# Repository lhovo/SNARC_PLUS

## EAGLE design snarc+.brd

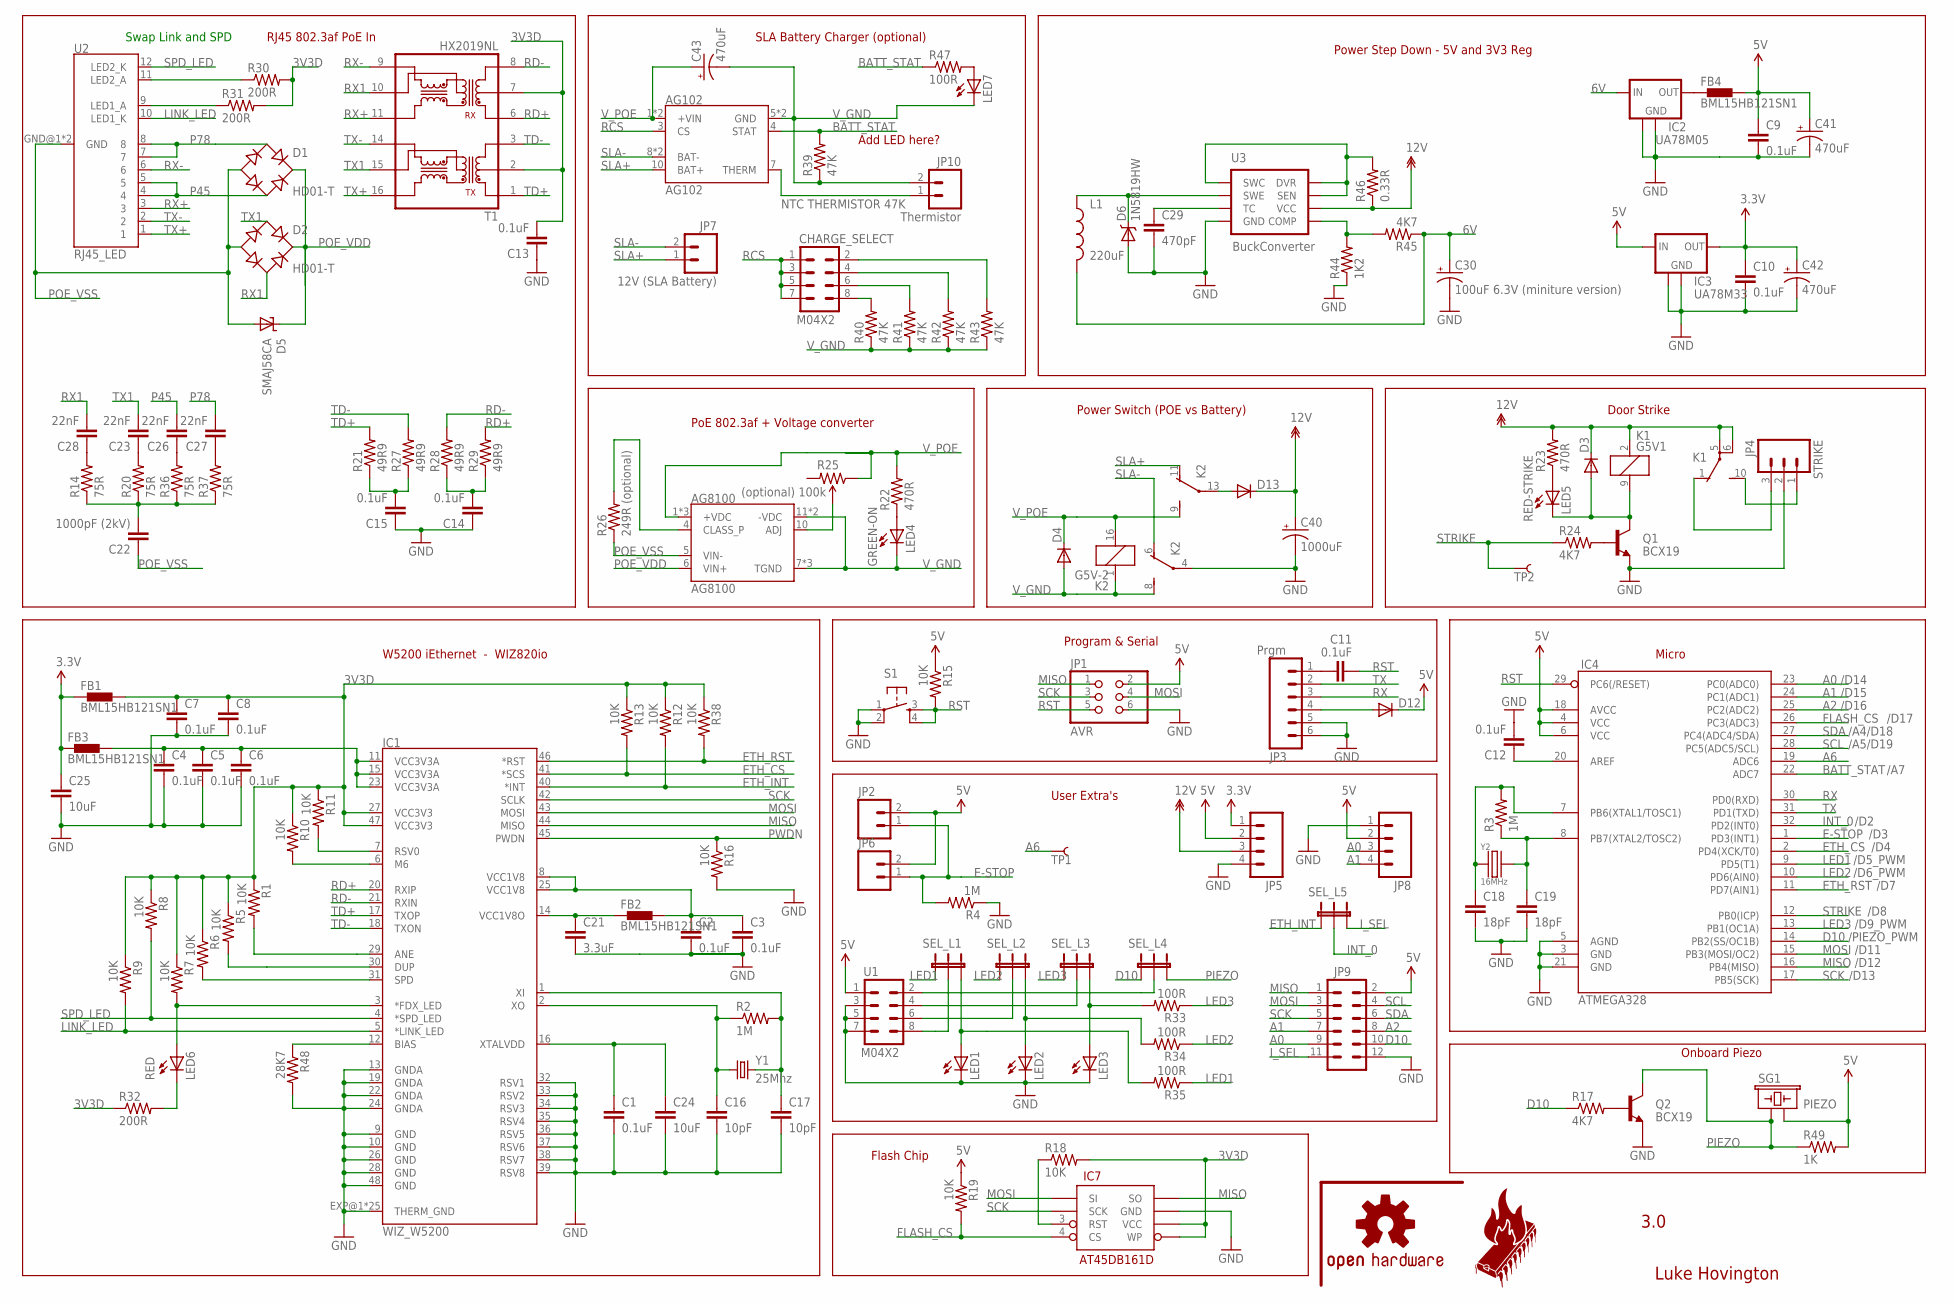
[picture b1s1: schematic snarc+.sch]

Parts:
AG102: AG102
AG8100: AG8100
C1, C2, C3, C4, C5, C6, C7, C8, C9, C10, C11, C12, C13, C14, C15: 0.1uF; 0402-CAP
C16, C17: 10pF; 0402-CAP
C18, C19: 18pF; 0402-CAP
C21: 3.3uF; 0402-CAP
C22: 1000pF (2kV); 0402-CAP
C23, C26, C27, C28: 22nF; 0402-CAP
C24, C25: 10uF; 0603-CAP
C29: 470pF; 0402-CAP
C30: 100uF 6.3V (miniture version); PANASONIC_C
C40: 1000uF; PANASONIC_H13
C41, C42, C43: 470uF; PANASONIC_E
CHARGE_SELECT: M04X2; 2X4
D1, D2: HD01-T; MBS
D3, D4, D12, D13: DIODESOD; SOD-323
D5: SMAJ58CA; SMBJ
D6: 1N5819HW; SOD-123
FB1, FB2, FB3, FB4: BML15HB121SN1; 0402
IC1: WIZ_W5200; QFN48
IC2: UA78M05; SOT223
IC3: UA78M33; SOT223
IC4: ATMEGA328; TQFP32-08
IC7: AT45DB161D; SO08-EIAJ
JP1: AVR; 2X03
JP2: M023.5MM; SCREWTERMINAL-3.5MM-2
JP3: Prgm; 1X06_SMD_STRAIGHT
JP4: STRIKE; SCREWTERMINAL-3.5MM-3
JP5: M04SMD; 1X04-SMD
JP6: M021X02_NO_SILK; 1X02_NO_SILK
JP7: 12V (SLA Battery); SCREWTERMINAL-3.5MM-2
JP8: M04POLAR; MOLEX-1X4
JP9: M05x2_SMD; 2X6-SHROUDED_SMD
JP10: Thermistor; SCREWTERMINAL-3.5MM-2
K1: G5V1; MPN G5V-1-DC24
K2: G5V-2
L1: 220uF; SRN
LED1, LED2, LED3, LED7: LED0603; LED-0603
LED4: GREEN-ON; LED-0603
LED5: RED-STRIKE; LED-0603
LED6: RED; LED-0603
Q1, Q2: BCX19; SOT23-3
R1, R5, R6, R7, R8, R9, R10, R11, R12, R13, R15, R16, R18, R19, R38: 10K; 0402-RES
R2, R3: 1M; 0402-RES
R4: 1M; 0603-RES
R14, R20, R36, R37: 75R; 0402-RES
R17, R24, R45: 4K7; 0402-RES
R21, R27, R28, R29: 49R9; 0402-RES
R22, R23: 470R; 0402-RES
R25: (optional) 100k; TRIMPOT-3MM
R26: 249R (optional); 1206
R30, R31, R32: 200R; 0402-RES
R33, R34, R35, R47: 100R; 0402-RES
R39, R40, R41, R42, R43: 47K; 0402-RES
R44: 1K2; 0402-RES
R46: 0.33R; 0402-RES
R48: 28K7; 0402-RES
R49: 1K; 0402-RES
S1: TAC_SWITCHSMD; TACTILE_SWITCH_SMD
SEL_L1, SEL_L2, SEL_L3, SEL_L4, SEL_L5: JUMPER-32-3; SJ_3_PASTE2&3
SG1: PIEZO; PB158-BUZZER
T1: HX2019NL; HXXXX
TP1, TP2: TEST-POINT3X5; PAD.03X.05
U1: M04X2; 2X4
U2: RJ45_LED; RJHSE-5484
U3: BuckConverter; SO08
U$15: OSHW-LOGOL; OSHW-LOGO-L
U$16: HSBNE_LOGOMED; HSBNE_MED
Y1: 25Mhz; CRYSTAL-SMD-2.5X2-ABM10
Y2: 16MHz; XTAL-CSX750

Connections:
3.3V: C10.1, C25.1, C42.+, FB1.1, FB3.1, IC3.3 (OUT), JP5.1
3V3A: C4.1, C5.1, C6.1, FB3.2, IC1.11 (VCC3V3A), IC1.15 (VCC3V3A), IC1.23 (VCC3V3A)
3V3D: C7.1, C8.1, C13.2, FB1.2, IC1.27 (VCC3V3), IC1.47 (VCC3V3), IC7.5 (WP), IC7.6 (VCC), R1.1, R5.1, R6.1, R7.1, R8.1, R9.1, R10.1, R11.1, R12.1, R13.1, R18.2, R30.2, R31.2, R32.1, R38.1, T1.2, T1.7
5V: C9.1, C41.+, D12.1 (C), FB4.2, IC3.1 (IN), IC4.4 (VCC), IC4.6 (VCC), IC4.18 (AVCC), JP1.2, JP2.2, JP5.2, JP6.2, JP8.2, JP9.2, R15.1, R19.1, R49.2, SG1.P$2 (2), U1.1
6V: C30.+, IC2.1 (IN), L1.P$2 (2), R45.1
12V: C40.+, D3.1 (C), D13.1 (C), JP5.3, K1.2 (1), K1.5, K1.6, R23.2, R46.1, U3.6 (VCC)
A0: IC4.23 (PC0(ADC0)), JP8.3, JP9.9
A1: IC4.24 (PC1(ADC1)), JP8.4, JP9.7
A2: IC4.25 (PC2(ADC2)), JP9.8
A6: IC4.19 (ADC6), TP1.P$1
AREF1: C12.1, IC4.20 (AREF)
BATT_STAT: AG102.4 (STAT), IC4.22 (ADC7), R39.2, R47.1
BATT_THERM: AG102.7 (THERM), JP10.1
D10: IC4.14 (PB2(SS/OC1B)), JP9.10, R17.1, SEL_L4.1
E-STOP: IC4.1 (PD3(INT1)), JP2.1, JP6.1, R4.2
ETH_CS: IC1.41 (*SCS), IC4.2 (PD4(XCK/T0)), R13.2
ETH_INT: IC1.40 (*INT), R12.2, SEL_L5.1
ETH_RST: IC1.46 (*RST), IC4.11 (PD7(AIN1)), R38.2
FDX_LED: IC1.3 (*FDX_LED), LED6.A, R7.2
FLASH_CS: IC4.26 (PC3(ADC3)), IC7.4 (CS), R19.2
GND: C1.2, C2.2, C3.2, C4.2, C5.2, C6.2, C7.2, C8.2, C9.2, C10.2, C12.2, C13.1, C14.1, C15.1, C16.2, C17.2, C18.2, C19.2, C21.2, C24.2, C25.2, C29.2, C30.-, C40.-, C41.-, C42.-, D6.2 (A), IC1.9 (GND), IC1.10 (GND), IC1.13 (GNDA), IC1.19 (GNDA), IC1.22 (GNDA), IC1.24 (GNDA), IC1.26 (GND), IC1.28 (GND), IC1.32 (RSV1), IC1.33 (RSV2), IC1.34 (RSV3), IC1.35 (RSV4), IC1.36 (RSV5), IC1.37 (RSV6), IC1.38 (RSV7), IC1.39 (RSV8), IC1.48 (GND), IC1.EXP@1 (THERM_GND), IC1.EXP@2 (THERM_GND), IC1.EXP@3 (THERM_GND), IC1.EXP@4 (THERM_GND), IC1.EXP@5 (THERM_GND), IC1.EXP@6 (THERM_GND), IC1.EXP@7 (THERM_GND), IC1.EXP@8 (THERM_GND), IC1.EXP@9 (THERM_GND), IC1.EXP@10 (THERM_GND), IC1.EXP@11 (THERM_GND), IC1.EXP@12 (THERM_GND), IC1.EXP@13 (THERM_GND), IC1.EXP@14 (THERM_GND), IC1.EXP@15 (THERM_GND), IC1.EXP@16 (THERM_GND), IC1.EXP@17 (THERM_GND), IC1.EXP@18 (THERM_GND), IC1.EXP@19 (THERM_GND), IC1.EXP@20 (THERM_GND), IC1.EXP@21 (THERM_GND), IC1.EXP@22 (THERM_GND), IC1.EXP@23 (THERM_GND), IC1.EXP@24 (THERM_GND), IC1.EXP@25 (THERM_GND), IC2.2 (GND), IC2.4 (GND1), IC3.2 (GND), IC3.4 (GND1), IC4.3 (GND), IC4.5 (AGND), IC4.21 (GND), IC7.7 (GND), JP1.6, JP3.5, JP3.6, JP4.2, JP5.4, JP8.1, JP9.12, K2.4, LED1.C, LED2.C, LED3.C, Q1.2 (E), Q2.2 (E), R4.1, R16.2, R44.1, R48.2, S1.1, S1.2, U1.3, U1.5, U1.7, U3.4 (GND)
INT_0: IC4.32 (PD2(INT0)), SEL_L5.2
I_SEL: JP9.11, SEL_L5.3
LED1: IC4.9 (PD5(T1)), R35.1, SEL_L1.1
LED2: IC4.10 (PD6(AIN0)), R34.1, SEL_L2.1
LED3: IC4.13 (PB1(OC1A)), R33.1, SEL_L3.1
LINK_LED: IC1.5 (*LINK_LED), R9.2, U2.10 (LED1_K)
MISO: IC1.44 (MISO), IC4.16 (PB4(MISO)), IC7.8 (SO), JP1.1, JP9.1
MOSI: IC1.43 (MOSI), IC4.15 (PB3(MOSI/OC2)), IC7.1 (SI), JP1.4, JP9.3
unnamed: IC1.12 (BIAS), R48.1
unnamed: C1.1, C24.1, IC1.16 (XTALVDD)
unnamed: IC1.6 (M6), R10.2
unnamed: C2.1, C3.1, FB2.2, IC1.8 (VCC1V8), IC1.25 (VCC1V8)
unnamed: C16.1, IC1.2 (XO), R2.1, Y1.P$1 (1)
unnamed: C17.1, IC1.1 (XI), R2.2, Y1.P$3 (2)
unnamed: IC1.29 (ANE), R1.2
unnamed: IC1.30 (DUP), R5.2
unnamed: C21.1, FB2.1, IC1.14 (VCC1V8O)
unnamed: IC1.31 (SPD), R6.2
unnamed: SEL_L3.2, U1.4
unnamed: IC1.7 (RSV0), R11.2
unnamed: LED6.C, R32.2
unnamed: LED7.A, R47.2
unnamed: C28.1, R14.2
unnamed: LED1.A, R35.2, SEL_L1.3
unnamed: AG8100.4 (CLASS_P), R26.2
unnamed: Q2.1 (B), R17.2
unnamed: C23.1, R20.2
unnamed: C22.2, R14.1, R20.1, R36.1, R37.1
unnamed: IC7.3 (RST), R18.1
unnamed: AG8100.10 (ADJ), R25.2 (WIPER)
unnamed: FB4.1, IC2.3 (OUT)
unnamed: R30.1, U2.11 (LED2_A)
unnamed: D13.2 (A), K2.13
unnamed: R31.1, U2.9 (LED1_A)
unnamed: C15.2, R21.1, R27.1
unnamed: C18.1, IC4.7 (PB6(XTAL1/TOSC1)), R3.2, Y2.1
unnamed: C19.1, IC4.8 (PB7(XTAL2/TOSC2)), R3.1, Y2.3
unnamed: C14.2, R28.1, R29.1
unnamed: C26.1, R36.2
unnamed: CHARGE_SELECT.8, R40.2
unnamed: CHARGE_SELECT.6, R41.2
unnamed: CHARGE_SELECT.4, R42.2
unnamed: CHARGE_SELECT.2, R43.2
unnamed: R44.2, R45.2, U3.5 (COMP)
unnamed: C27.1, R37.2
unnamed: SEL_L1.2, U1.8
unnamed: C11.2, JP3.1
unnamed: R46.2, U3.1 (SWC), U3.7 (SEN), U3.8 (DVR)
unnamed: LED2.A, R34.2, SEL_L2.3
unnamed: D6.1 (C), L1.P$1 (1), U3.2 (SWE)
unnamed: C29.1, U3.3 (TC)
unnamed: LED3.A, R33.2, SEL_L3.3
unnamed: D12.2 (A), JP3.4
unnamed: D3.2 (A), K1.9 (2), LED5.C, Q1.3 (C)
unnamed: Q1.1 (B), R24.2
unnamed: LED5.A, R23.1
unnamed: LED4.A, R22.1
unnamed: SEL_L2.2, U1.6
unnamed: SEL_L4.2, U1.2
P45: C26.2, D1.AC2, U2.4, U2.5
P78: C27.2, D1.AC1, U2.7, U2.8
PIEZO: Q2.3 (C), R49.1, SEL_L4.3, SG1.P$1 (1)
POE_VDD: AG8100.6 (VIN+), D1.+, D2.+, D5.C
POE_VSS: AG8100.5 (VIN-), C22.1, D1.-, D2.-, D5.A, R26.1, U2.GND@1 (GND), U2.GND@2 (GND)
PWDN: IC1.45 (PWDN), R16.1
RCS: AG102.3 (CS), CHARGE_SELECT.1, CHARGE_SELECT.3, CHARGE_SELECT.5, CHARGE_SELECT.7
RD+: IC1.20 (RXIP), R29.2, T1.6
RD-: IC1.21 (RXIN), R28.2, T1.8
RST: C11.1, IC4.29 (PC6(/RESET)), JP1.5, R15.2, S1.3, S1.4
RX: IC4.30 (PD0(RXD)), JP3.3
RX1: C28.2, D2.AC2, T1.10
RX+: T1.11, U2.3
RX-: T1.9, U2.6
SCK: IC1.42 (SCLK), IC4.17 (PB5(SCK)), IC7.2 (SCK), JP1.3, JP9.5
SCL: IC4.28 (PC5(ADC5/SCL)), JP9.4
SDA: IC4.27 (PC4(ADC4/SDA)), JP9.6
SLA+: AG102.10 (BAT+), JP7.1, K2.11 (O)
SLA-: AG102.8 (BAT-), AG102.9 (BAT-), JP7.2, K2.6 (O)
SPD_LED: IC1.4 (*SPD_LED), R8.2, U2.12 (LED2_K)
STRIKE: IC4.12 (PB0(ICP)), R24.1, TP2.P$1
STRIKE_NC: JP4.3, K1.1 (O)
STRIKE_NO: JP4.1, K1.10 (S)
TD+: IC1.17 (TXOP), R21.2, T1.1
TD-: IC1.18 (TXON), R27.2, T1.3
TX: IC4.31 (PD1(TXD)), JP3.2
TX1: C23.2, D2.AC1, T1.15
TX+: T1.16, U2.1
TX-: T1.14, U2.2
V_GND: AG102.5 (GND), AG102.6 (GND), AG8100.7 (TGND), AG8100.8 (TGND), AG8100.9 (TGND), AG8100.11 (-VDC), AG8100.12 (-VDC), C43.-, D4.2 (A), JP10.2, K2.1, K2.8 (S), LED4.C, LED7.C, R39.1, R40.1, R41.1, R42.1, R43.1
V_POE: AG102.1 (+VIN), AG102.2 (+VIN), AG8100.1 (+VDC), AG8100.2 (+VDC), AG8100.3 (+VDC), C43.+, D4.1 (C), K2.9 (S), K2.16 (2), R22.2, R25.1 (CCW)

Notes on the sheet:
RJ45 802.3af PoE In
W5200 iEthernet - WIZ820io
Power Step Down - 5V and 3V3 Reg
Luke Hovington
3.0
Program & Serial
Door Strike
User Extra's
Power Switch (POE vs Battery)
/D11
/D12
/D13
/D3
/D5_PWM
/D6_PWM
/D4
/D2
/PIEZO_PWM
/D9_PWM
/D8
/D7
Flash Chip
Swap Link and SPD
Micro
/A4/D18
/A5/D19
/D17
PoE 802.3af + Voltage converter
SLA Battery Charger (optional)
NTC THERMISTOR 47K
/A7
Add LED here?
/D16
/D15
/D14
Onboard Piezo

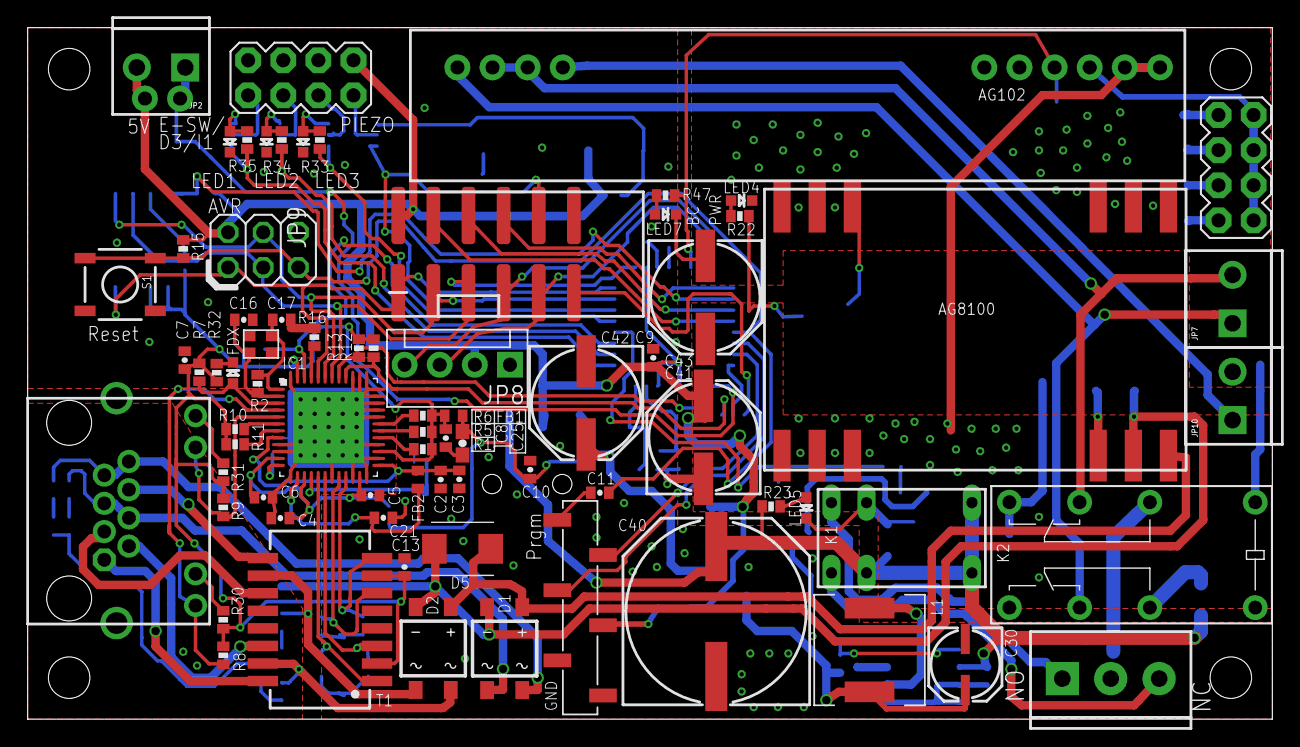
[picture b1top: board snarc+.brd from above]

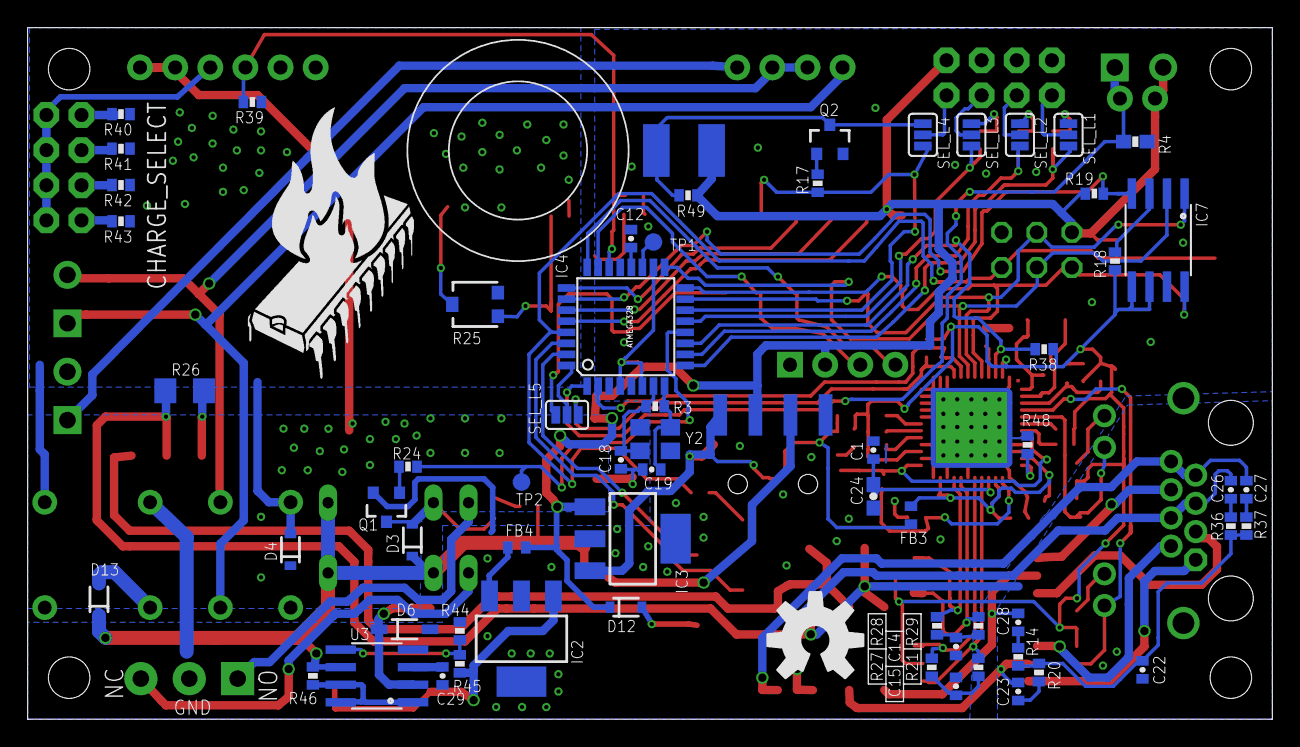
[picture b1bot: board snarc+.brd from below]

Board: 4 copper layers, 90.0 x 50.0 mm, 141 parts (66 on the bottom side), 111 nets.

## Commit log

2013-04-04 New snarc V3

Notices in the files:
parts and their libraries:
SparkFun-Connectors: Licensing: CC v3.0 Share-Alike You are welcome to use this library for commercial purposes.
